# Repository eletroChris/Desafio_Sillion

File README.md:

# Desafio Sillion

## Descrição
O objetivo do projeto é controlar um pequeno motor DC de 5V utilizando um microcontronlador. Para realizar a interface com o operador, deve ser utilizado um display LCD 16x2.  

Nessa atividade um push button ligado ao microcontrolador ativa o motor por 10 segundos a cada acionamento. O display informa ao operador sobre o estado do motor com as mensagens ***Motor Ligado*** e ***Motor Desligado***. O microcontrolador utilizado no projeto foi o AT89C51. 

O circuito e o layout da placa foram criados usando o software KiCAD. 

## Organização dos arquivos

No primeiro nível do diretório encontram-se:

* Esquemático do circuito: ***Circuito_Controle_Motor.pdf***
* O código em C para o microcontrolador AT89C51: ***MotorDC_controle.c***
* Um screenshot do layout da placa: ***Placa_Layout.pdf***
* Um modelo 3D aproximado do circuito pronto. (Alguns componentes não possuem modelo 3D, por isso não estão presentes na imagem): ***Controle_Motor_DC_3D.png***

* O folder Datasheets, onde encontram-se os datasheets dos principais componentes do circuito.

* O folder Controle_Motor_DC, onde encontram-se os arquivos gerber e os arquivos gerados pelo Kicad.

Os arquivos gerber para produção da placa estão no caminho ***Controle_Motor_DC/Controle_Motor_DC/Gerber_Files***

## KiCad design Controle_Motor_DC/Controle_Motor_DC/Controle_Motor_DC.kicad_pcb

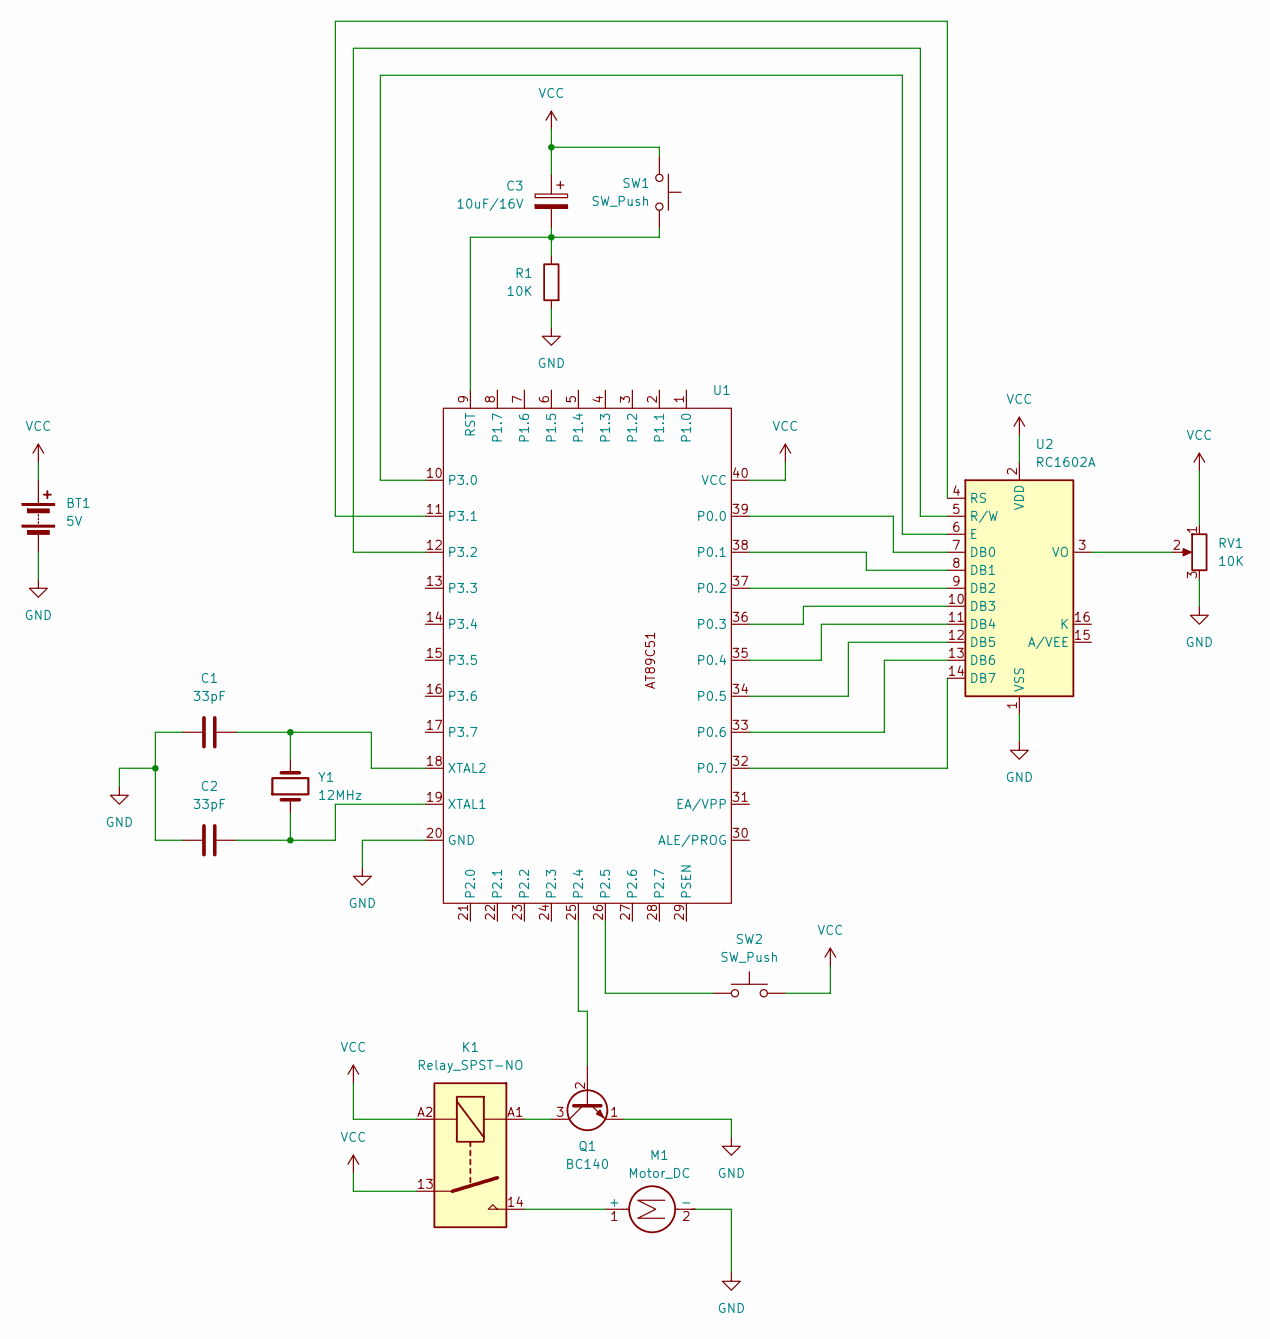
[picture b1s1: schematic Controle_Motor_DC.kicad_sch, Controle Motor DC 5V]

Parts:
BT1: 5V; BarrelJack_CUI_PJ-063AH_Horizontal
C1, C2: 33pF; C_Rect_L4.0mm_W2.5mm_P2.50mm
C3: 10uF/16V; CP_Radial_D5.0mm_P2.50mm
K1: Relay_SPST-NO; Relay_COMUS_3570_1331
M1: Motor_DC; PhoenixContact_GMSTBV_2,5_2-GF-7,62_1x02_P7.62mm_Vertical_T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
Q1: BC140; TO-39-3
R1: 10K; R_Axial_DIN0207_L6.3mm_D2.5mm_P7.62mm_Horizontal
RV1: 10K; Potentiometer_ACP_CA6-H2,5_Horizontal
SW1, SW2: SW_Push; SW_PUSH-12mm_Wuerth-430476085716
U1: AT89C51-PDIP
U2: RC1602A
Y1: 12MHz; Resonator-2Pin_W10.0mm_H5.0mm

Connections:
GND: BT1.2 (-), C1.2, C2.2, M1.2 (-), Q1.1 (E), R1.2, RV1.3, U1.20 (GND), U2.1 (VSS)
unnamed: K1.14, M1.1 (+)
unnamed: Q1.2 (B), U1.25 (P2.4)
unnamed: K1.A1, Q1.3 (C)
unnamed: U1.39 (P0.0), U2.7 (DB0)
unnamed: U1.38 (P0.1), U2.8 (DB1)
unnamed: U1.37 (P0.2), U2.9 (DB2)
unnamed: U1.36 (P0.3), U2.10 (DB3)
unnamed: U1.35 (P0.4), U2.11 (DB4)
unnamed: U1.34 (P0.5), U2.12 (DB5)
unnamed: U1.33 (P0.6), U2.13 (DB6)
unnamed: U1.32 (P0.7), U2.14 (DB7)
unnamed: SW2.2, U1.26 (P2.5)
unnamed: U1.10 (P3.0), U2.6 (E)
unnamed: U1.11 (P3.1), U2.4 (RS)
unnamed: U1.12 (P3.2), U2.5 (R/W)
unnamed: C3.2, R1.1, SW1.1, U1.9 (RST)
unnamed: C2.1, U1.19 (XTAL1), Y1.1
unnamed: C1.1, U1.18 (XTAL2), Y1.2
unnamed: RV1.2, U2.3 (VO)
VCC: BT1.1 (+), C3.1, K1.13, K1.A2, RV1.1, SW1.2, SW2.1, U1.40 (VCC), U2.2 (VDD)

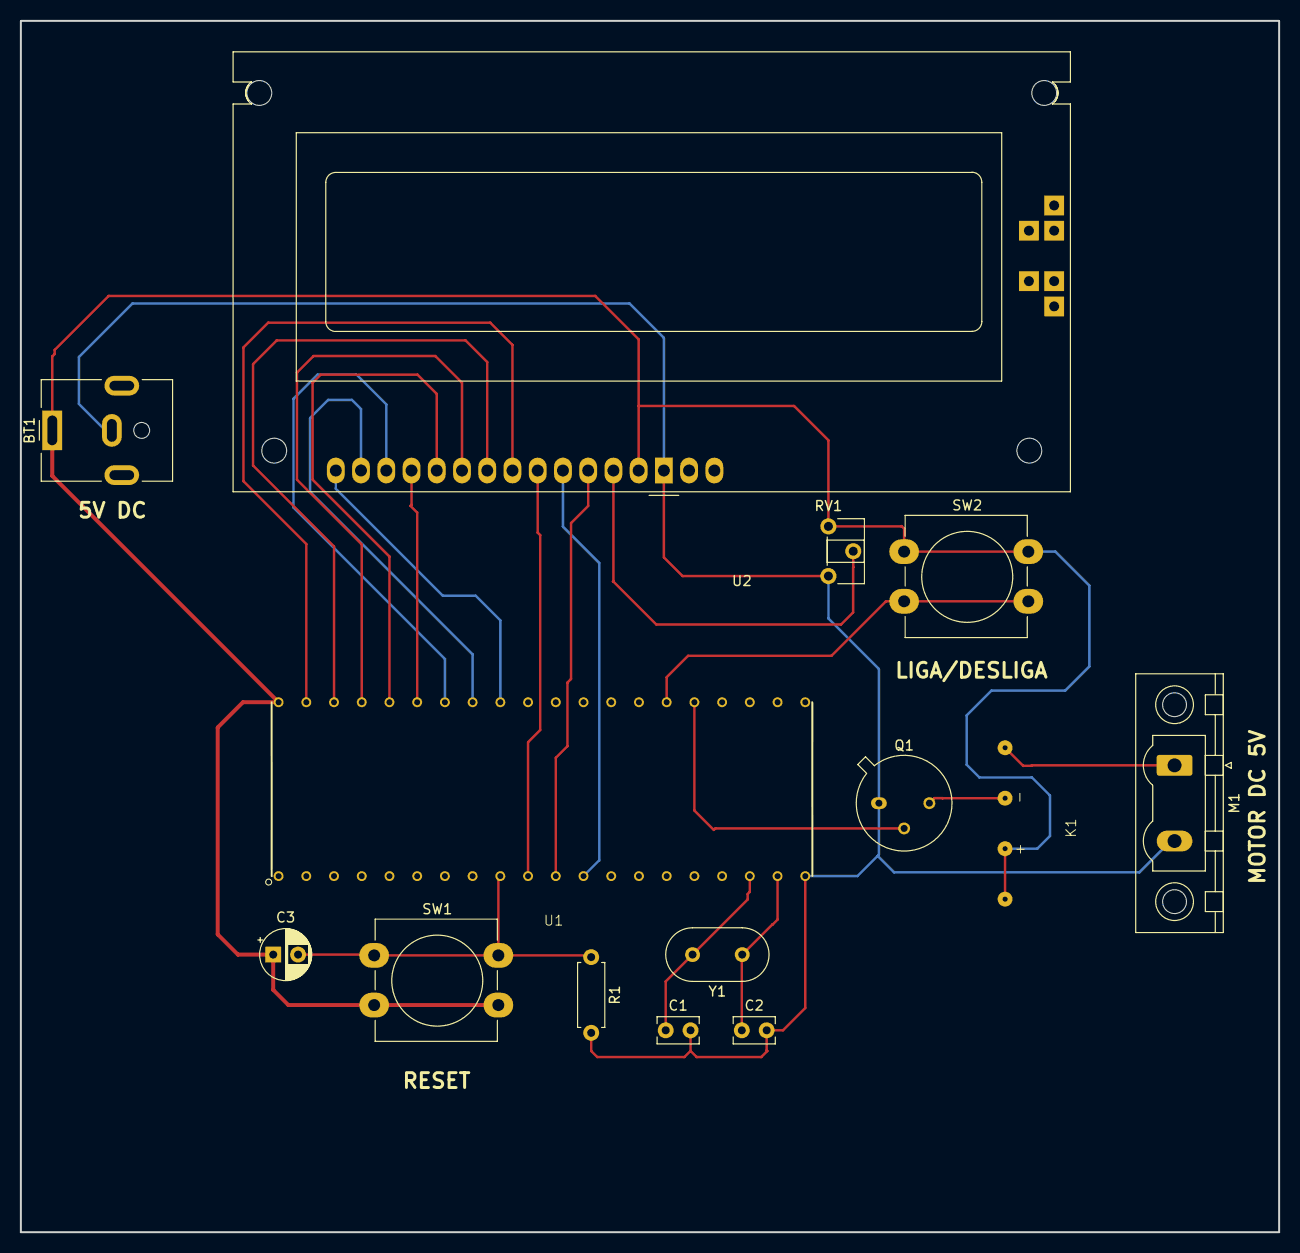
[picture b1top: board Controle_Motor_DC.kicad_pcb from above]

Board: 2 copper layers, 126.6 x 121.9 mm, 14 parts (0 on the bottom side), 21 nets.

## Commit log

2023-12-14 Primeiro commit. Adicionando código C, datasheets e arquivos do KiCAD
2023-12-14 Primeira versão do README
2023-12-15 Adição dos arquivos gerber, atualização do README, adição da imagem do modelo 3D da placa
